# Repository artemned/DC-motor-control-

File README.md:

# DC-motor-control
### *Hello everyone, I want to share with you my device. This is a DC motor control board. The board is multifunctional and you can verify this by looking at the circuit diagram and the software part. This functionality can be added as needed: connecting sensors, necessary peripherals and adding the software part.*
## *The board looks like :* 

### *In the “DriverBoardCode” directory, in addition to the sources and the hex file of the firmware, there is also a zip file of the project, which was created using Microchip Studio.*

### *I use it for my own wood lathe, which is shown in the render in the “BoardImages” directory. The machine is called "Eaglet".*
## *The Eaglet looks like :*

### *P.S. Everyone goodness and fresh cookies!*
### *License: [Free license](https://github.com/artemned/DC-motor-control-/blob/main/LICENSE)*
### *Email address for feedback: daineko.a32@mail.ru*

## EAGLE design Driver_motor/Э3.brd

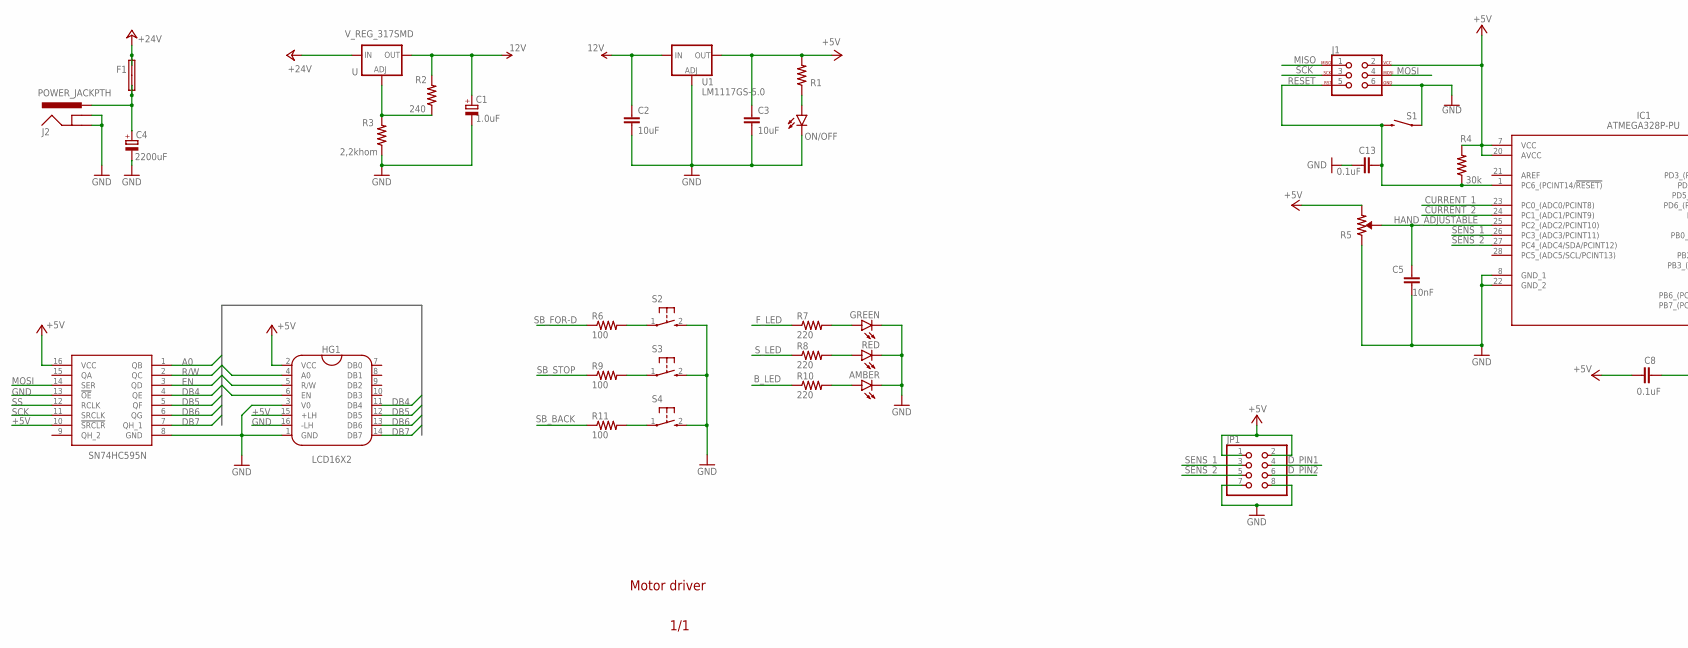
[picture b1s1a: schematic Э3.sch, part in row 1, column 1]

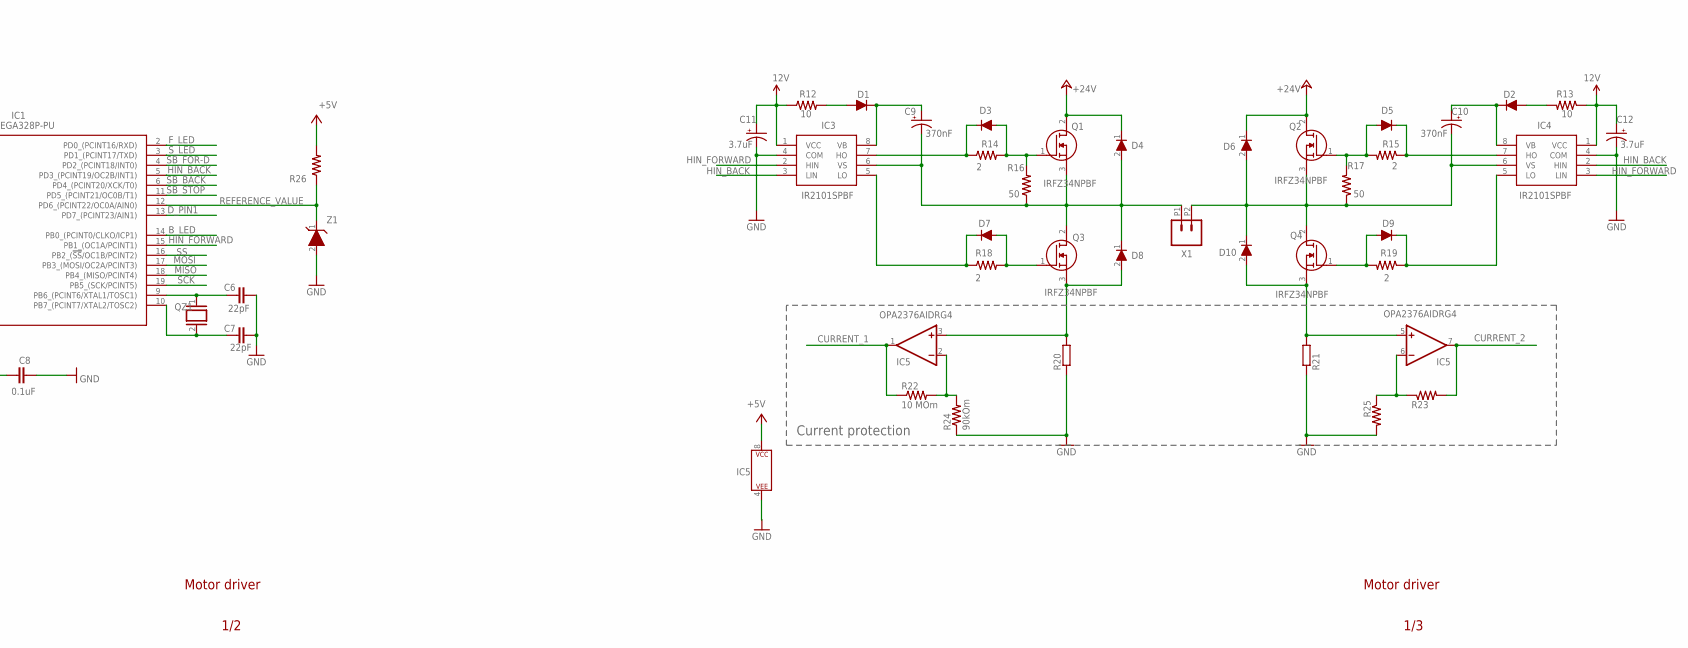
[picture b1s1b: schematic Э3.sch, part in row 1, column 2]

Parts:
AMBER: LED-3MM-NO_SILK; LED3MM-NS
C1: 1.0uF; E2,5-6E
C2, C3: 10uF; C1206
C4: 2200uF; E5-10,5
C5: 10nF; C1206
C6, C7: 22pF; CAP-PTH-2.54
C8, C13: 0.1uF; C1206
C9, C10: 370nF; SMC_A
C11, C12: 3.7uF; SMC_A
D1, D2: MURA110T3G; DIOM5226X220N
D3, D5, D7, D9: MBR0530T1G; SOD3716X135N
D4, D6, D8, D10: 1N4007E-E3_73; DIOAD1405W86L465D235
F1: SHK20L
GREEN: LED-3MM-NO_SILK; LED3MM-NS
HG1: LCD16X2; 1X16
IC1: ATMEGA328P-PU; DIP794W53P254L3467H457Q28N
IC2: SN74HC595N; DIP794W53P254L1930H508Q16N
IC3, IC4: IR2101SPBF; SOIC127P600X175-8N
IC5: OPA2376AIDRG4; SOIC127P600X175-8N
J1: AVR_SPI_PROG_3X2PTH; 2X3
J2: POWER_JACKPTH; POWER_JACK_PTH
JP1: PINHD-2X4; 2X04
ON/OFF: LED-3MM-NO_SILK; LED3MM-NS
Q1, Q2, Q3, Q4: IRFZ34NPBF; TO254P469X1042X1967-3P
QZ1: XTAL/S; QS
R1: 200; R1206
R2: 240; R1206
R3: 2,2khom; R1206
R4: 30k; R1206
R5: TRIMM_POT
R6, R9, R11: 100; R1206
R7, R8, R10: 220; R1206
R12, R13: 10; R1206
R14, R15, R18, R19: 2; 0207/7
R16, R17: 50; 0207/7
R20, R21: R-EU_R2512; R2512
R22: 10 MOm; R1206
R23, R25: R-US_R1206; R1206
R24: 90kOm; R1206
R26: 7; R1206
RED: LED-3MM-NO_SILK; LED3MM-NS
S1: MOMENTARY-SWITCH-SPST-PTH-6.0MM; TACTILE_SWITCH_PTH_6.0MM
S2, S3, S4: TAC_SWITCH_SPECIAL; TACTILE-SPECIAL_PTH
U: V_REG_317SMD; SOT223
U1: LM1117GS-5.0; SOT223
X1: DG340MY""; 1X02_3.81_SCREWTERM
Z1: BZV55C3V6-TP"""; BAQ33GS08

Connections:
12V: C1.+, C2.1, C11.+, C12.+, IC3.1 (VCC), IC4.1 (VCC), R2.2, R12.1, R13.1, U.2 (OUT), U1.3 (IN)
+5V: C3.1, C8.1, HG1.2 (VCC), HG1.15 (+LH), IC1.7 (VCC), IC1.20 (AVCC), IC2.10 (!SRCLR), IC2.16 (VCC), IC5.8 (P$V+), J1.2, JP1.1, JP1.2, R1.2, R4.2, R5.1 (CCW), R26.2, U1.2 (OUT), U1.4 (OUT)
+24V: D4.1 (K), D6.1 (K), F1.2A, F1.2B, Q1.2 (D), Q2.2 (D), U.3 (IN)
A0: HG1.4 (A0), IC2.1 (QB)
B_LED: IC1.14 (PB0_(PCINT0/CLKO/ICP1)), R10.1
CURRENT_1: IC1.23 (PC0_(ADC0/PCINT8)), IC5.1 (OUT), R22.1
CURRENT_2: IC1.24 (PC1_(ADC1/PCINT9)), IC5.7 (OUT), R23.2
DB4: HG1.11 (DB4), IC2.4 (QE)
DB5: HG1.12 (DB5), IC2.5 (QF)
DB6: HG1.13 (DB6), IC2.6 (QG)
DB7: HG1.14 (DB7), IC2.7 (QH_1)
D_PIN1: IC1.13 (PD7_(PCINT23/AIN1)), JP1.4
D_PIN2: JP1.6
EN: HG1.6 (EN), IC2.3 (QD)
F_LED: IC1.2 (PD0_(PCINT16/RXD)), R7.1
GND: AMBER.K (C), C1.-, C2.2, C3.2, C4.-, C5.2, C6.2, C7.2, C8.2, C11.-, C12.-, C13.2, GREEN.K (C), HG1.1 (GND), HG1.3 (V0), HG1.16 (-LH), IC1.8 (GND_1), IC1.22 (GND_2), IC2.8 (GND), IC2.13 (!OE), IC3.4 (COM), IC4.4 (COM), IC5.4 (P$V-), J1.6, J2.GND, J2.GNDBREAK, JP1.7, JP1.8, ON/OFF.K (C), R3.1, R5.3 (CW), R20.1, R21.1, R24.1, R25.2, RED.K (C), S1.1, S2.2 (3), S3.2 (3), S4.2 (3), U1.1 (ADJ), Z1.2 (A)
HAND_ADJUSTABLE: C5.1, IC1.25 (PC2_(ADC2/PCINT10)), R5.2 (WIPER)
HIN_BACK: IC1.5 (PD3_(PCINT19/OC2B/INT1)), IC3.3 (LIN), IC4.2 (HIN)
HIN_FORWARD: IC1.15 (PB1_(OC1A/PCINT1)), IC3.2 (HIN), IC4.3 (LIN)
MISO: IC1.18 (PB4_(MISO/PCINT4)), J1.1
MOSI: IC1.17 (PB3_(MOSI/OC2A/PCINT3)), IC2.14 (SER), J1.4
unnamed: ON/OFF.A, R1.1
unnamed: C4.+, F1.1A, F1.1B, J2.PWR
unnamed: D8.2 (A), IC5.3 (+IN), Q3.3 (S), R20.2
unnamed: D10.2 (A), IC5.5 (+IN), Q4.3 (S), R21.2
unnamed: GREEN.A, R7.2
unnamed: R8.2, RED.A
unnamed: AMBER.A, R10.2
unnamed: R2.1, R3.2, U.1 (ADJ)
unnamed: R6.2, S2.1
unnamed: R9.2, S3.1
unnamed: R11.2, S4.1
unnamed: C6.1, IC1.9 (PB6_(PCINT6/XTAL1/TOSC1)), QZ1.1
unnamed: C10.+, D2.1 (K), IC4.8 (VB)
unnamed: C7.1, IC1.10 (PB7_(PCINT7/XTAL2/TOSC2)), QZ1.2
unnamed: C9.+, D1.1 (K), IC3.8 (VB)
unnamed: IC5.2 (-IN), R22.2, R24.2
unnamed: C9.-, D4.2 (A), D8.1 (K), IC3.6 (VS), Q1.3 (S), Q3.2 (D), R16.1, X1.P1 (1)
unnamed: IC5.6 (-IN), R23.1, R25.1
unnamed: D1.2 (A), R12.2
unnamed: D3.1 (K), IC3.7 (HO), R14.1
unnamed: D3.2 (A), Q1.1 (G), R14.2, R16.2
unnamed: D7.2 (A), Q3.1 (G), R18.2
unnamed: D7.1 (K), IC3.5 (LO), R18.1
unnamed: D2.2 (A), R13.2
unnamed: C10.-, D6.2 (A), D10.1 (K), IC4.6 (VS), Q2.3 (S), Q4.2 (D), R17.1, X1.P2 (2)
unnamed: D5.1 (K), IC4.7 (HO), R15.1
unnamed: D5.2 (A), Q2.1 (G), R15.2, R17.2
unnamed: D9.2 (A), Q4.1 (G), R19.2
unnamed: D9.1 (K), IC4.5 (LO), R19.1
R/W: HG1.5 (R/W), IC2.2 (QC)
REFERENCE_VALUE: IC1.12 (PD6_(PCINT22/OC0A/AIN0)), R26.1, Z1.1 (K)
RESET: C13.1, IC1.1 (PC6_(PCINT14/!RESET)), J1.5, R4.1, S1.3 (2)
SB_BACK: IC1.6 (PD4_(PCINT20/XCK/T0)), R11.1
SB_FOR-D: IC1.4 (PD2_(PCINT18/INT0)), R6.1
SB_STOP: IC1.11 (PD5_(PCINT21/OC0B/T1)), R9.1
SCK: IC1.19 (PB5_(SCK/PCINT5)), IC2.11 (SRCLK), J1.3
SENS_1: IC1.26 (PC3_(ADC3/PCINT11)), JP1.3
SENS_2: IC1.27 (PC4_(ADC4/SDA/PCINT12)), JP1.5
SS: IC1.16 (PB2_(!SS!/OC1B/PCINT2)), IC2.12 (RCLK)
S_LED: IC1.3 (PD1_(PCINT17/TXD)), R8.1

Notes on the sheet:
IC5
Current protection
Motor driver
1/3
1/2
1/1

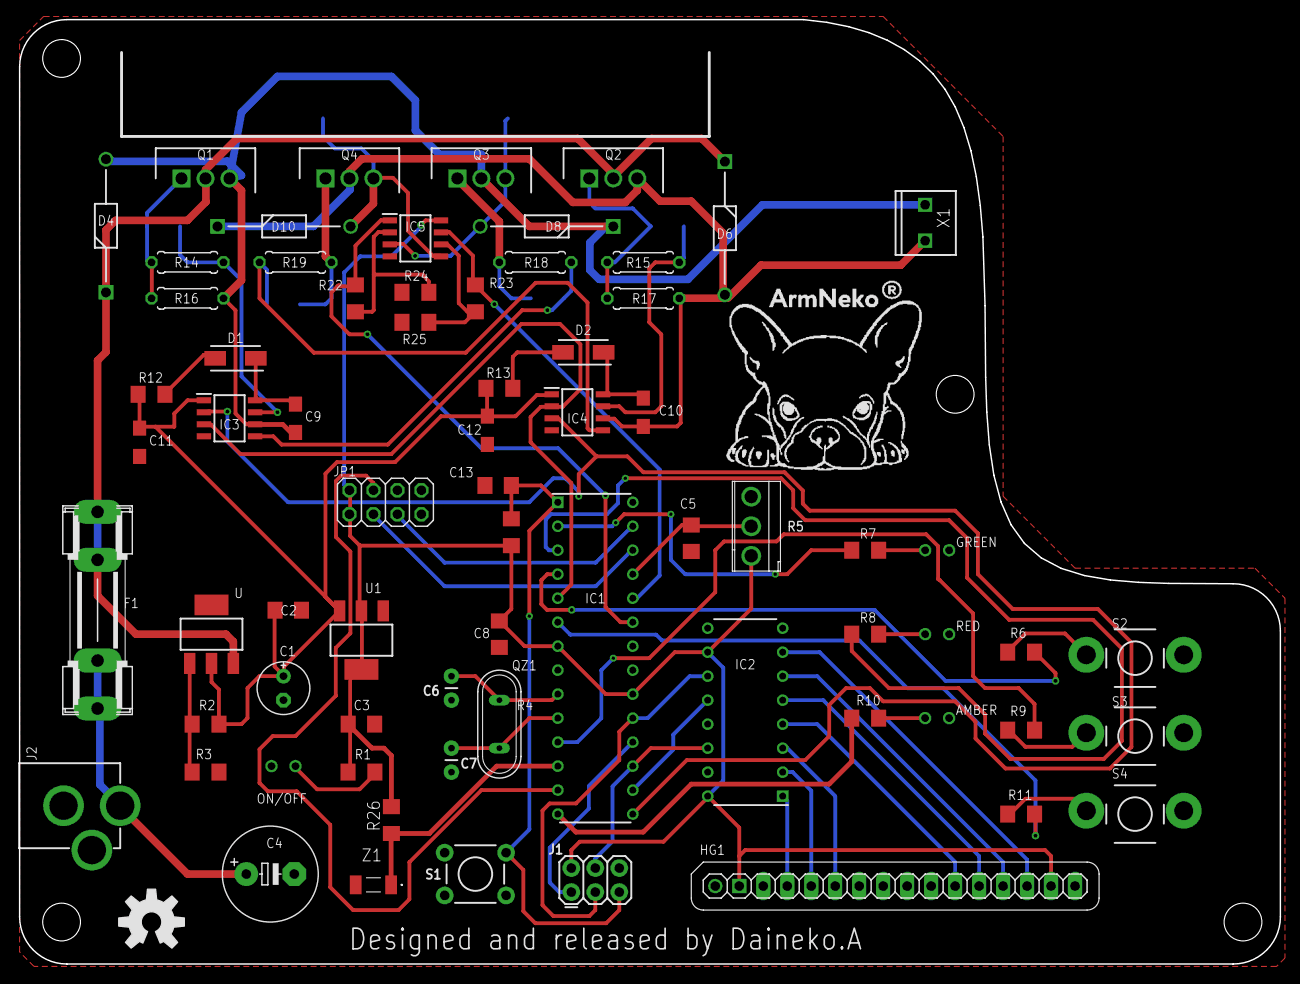
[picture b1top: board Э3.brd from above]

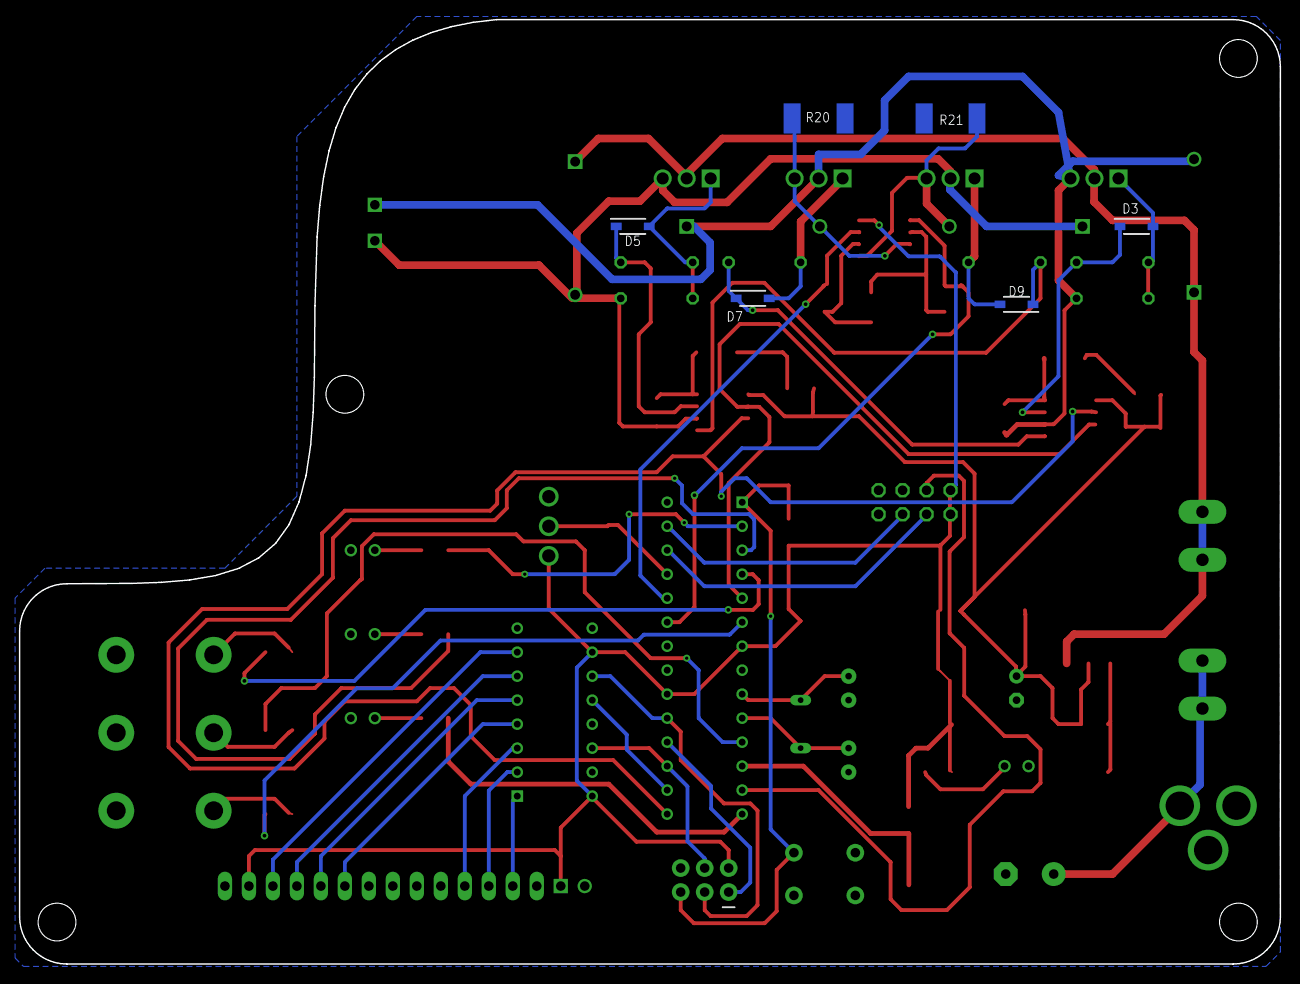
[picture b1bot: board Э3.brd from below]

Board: 2 copper layers, 133.5 x 100.0 mm, 77 parts (6 on the bottom side), 60 nets.

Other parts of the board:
U$1: OSHW-LOGO-L

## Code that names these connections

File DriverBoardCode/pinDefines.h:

/********************************************************************
	created:	2022/07/01
	created:	1:7:2022   10:58
	filename: 	C:\Users\sWe\Documents\Atmel Studio\7.0\pinDefines.h
	file path:	C:\Users\sWe\Documents\Atmel Studio\7.0
	file base:	pinDefines
	file ext:	h
	author:		ArtNeko
	
	purpose:	
*********************************************************************/
#pragma once
#include <avr/io.h>
#include "Bit_manip.h"

#define F_LED PD0
#define S_LED PD1
#define B_LED PB0
#define SB_FORD PD2
#define SB_BACK PD4
#define SB_STOP PD5
#define HIN_FORWARD PB1
#define HIN_BACK PD3
#define REF_VALUE PD6
#define D_PIN PD7

#define CURRENT_VALUE_1 PC0
#define CURRENT_VALUE_2 PC1
#define HAND_ADJUSTABLE PC2
#define SENS_1 PC3
#define SENS_2 PC4

#define DIRECTION_PORTS_D DDRD
#define READ_PIN_D PIND
#define CONFIGURATION_PORTS_D PORTD

#define DIRECTION_PORTS_B DDRB
#define READ_PIN_B PINB
#define CONFIGURATION_PORTS_B PORTB 

#define DIRECTION_PORTS_C DDRC
#define READ_PIN_C PINC
#define CONFIGURATION_PORTS_C PORTC

////////////////Analog registrs////////////////////
#define CONTROL_STATE_REGISTER_A ADCSRA
#define CONTROL_STATE_REGISTER_B ADCSRB
#define ANALOG_COMP_STATE_REGISTR ACSR
#define MUX_SELECTION_REGISTER ADMUX
#define DIGITAL_INPUT_DISABLE_0 DIDR0
#define DIGITAL_INPUT_DISABLE_1 DIDR1 
/////////Voltage edge////////////////////////////
#define REFERENCE_VOLTAGE 4.93
#define MAXIMUM_VALUE 3.3

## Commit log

2022-09-27 Add files via upload
    files with code
2022-09-27 Add files via upload
    This files for successful compilation
2022-09-28 Download full project
    Download full project

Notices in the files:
parts and their libraries:
SparkFun-Capacitors: Licensing: Creative Commons ShareAlike 4.0 International - https://creativecommons.org/licenses/by-sa/4.0
